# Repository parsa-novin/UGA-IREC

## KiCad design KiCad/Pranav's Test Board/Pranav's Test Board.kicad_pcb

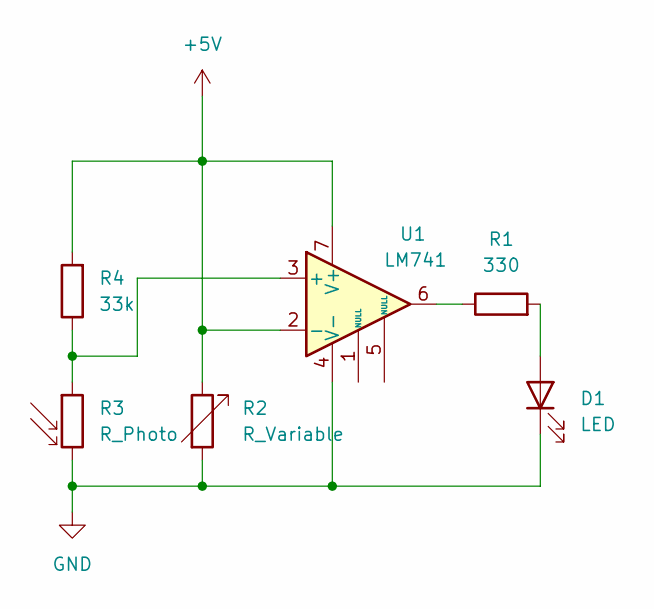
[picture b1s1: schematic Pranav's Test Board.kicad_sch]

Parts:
D1: LED; D_0201_0603Metric_Pad0.64x0.40mm_HandSolder
R1: 330; R_0201_0603Metric_Pad0.64x0.40mm_HandSolder
R2: R_Variable; R_0201_0603Metric_Pad0.64x0.40mm_HandSolder
R3: R_Photo; R_0201_0603Metric_Pad0.64x0.40mm_HandSolder
R4: 33k; R_0201_0603Metric_Pad0.64x0.40mm_HandSolder
U1: LM741; LM-741

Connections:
+5V: R2.1, R4.2, U1.2 (-), U1.7 (V+)
GND: D1.1 (K), R2.2, R3.2, U1.4 (V-)
unnamed: D1.2 (A), R1.2
unnamed: R1.1, U1.6
unnamed: R3.1, R4.1, U1.3 (+)

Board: 2 copper layers, 6 parts (0 on the bottom side), 5 nets, no tracks yet.

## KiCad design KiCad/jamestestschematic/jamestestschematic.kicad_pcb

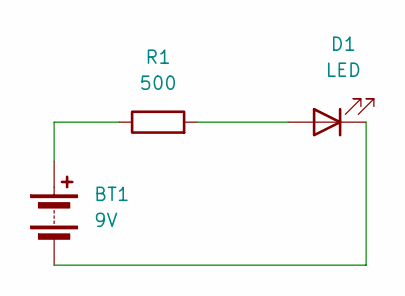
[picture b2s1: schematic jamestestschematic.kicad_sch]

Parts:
BT1: 9V; BatteryHolder_MPD_BC12AAPC_2xAA
D1: LED; LED_D5.0mm
R1: 500; R_Axial_DIN0414_L11.9mm_D4.5mm_P15.24mm_Horizontal

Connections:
unnamed: BT1.1 (+), R1.1
unnamed: BT1.2 (-), D1.1 (K)
unnamed: D1.2 (A), R1.2

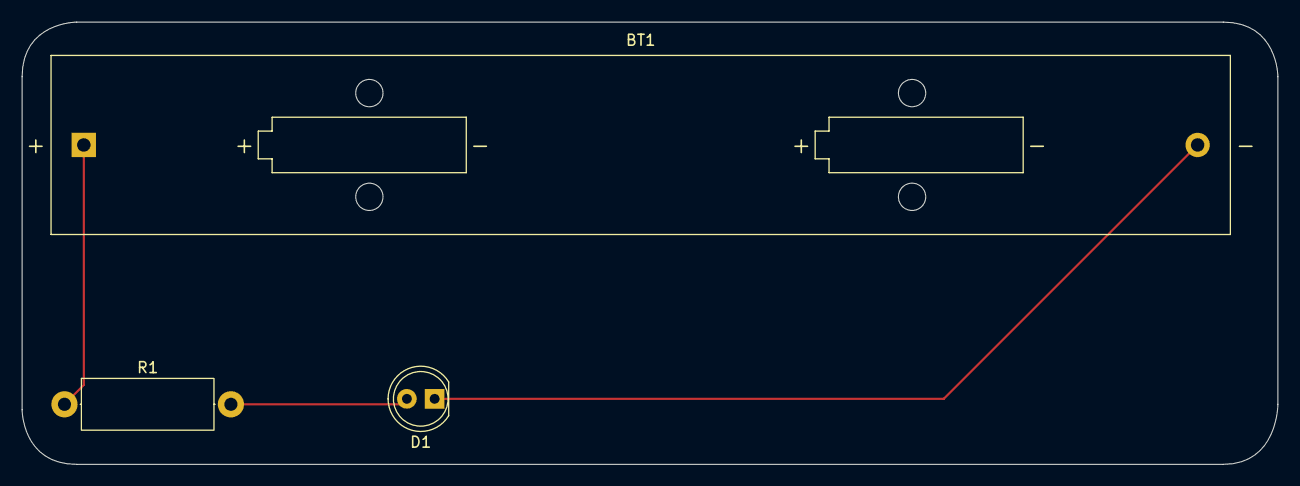
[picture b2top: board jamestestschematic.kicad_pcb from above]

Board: 2 copper layers, 115.0 x 40.5 mm, 3 parts (0 on the bottom side), 3 nets.

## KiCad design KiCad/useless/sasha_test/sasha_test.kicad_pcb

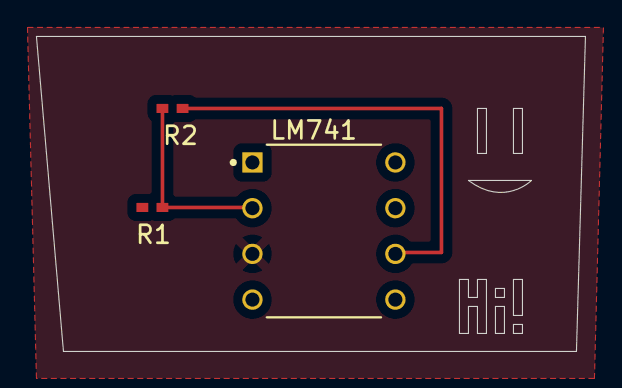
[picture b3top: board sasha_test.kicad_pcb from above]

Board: 2 copper layers, 30.5 x 17.5 mm, 3 parts (0 on the bottom side), 2 nets.

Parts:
LM741: LM741CN_NOPB; DIP794W45P254L959H508Q8
R1, R2: 1K; RC0402N_YAG

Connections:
unnamed: LM741.2 (INV_INPUT), R1.2, R2.1
unnamed: LM741.6 (OUTPUT), R2.2
